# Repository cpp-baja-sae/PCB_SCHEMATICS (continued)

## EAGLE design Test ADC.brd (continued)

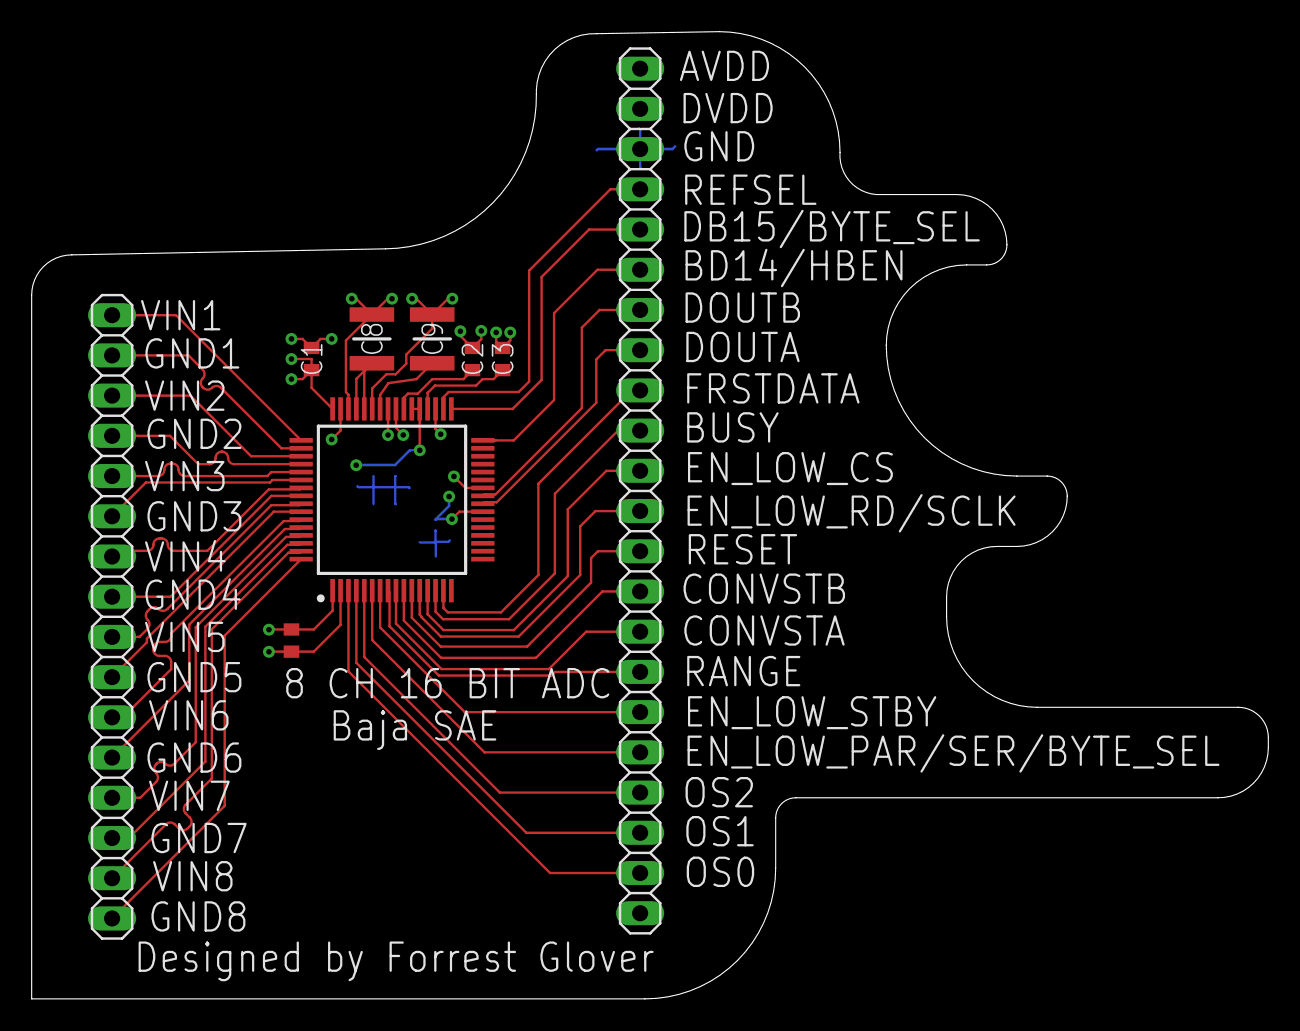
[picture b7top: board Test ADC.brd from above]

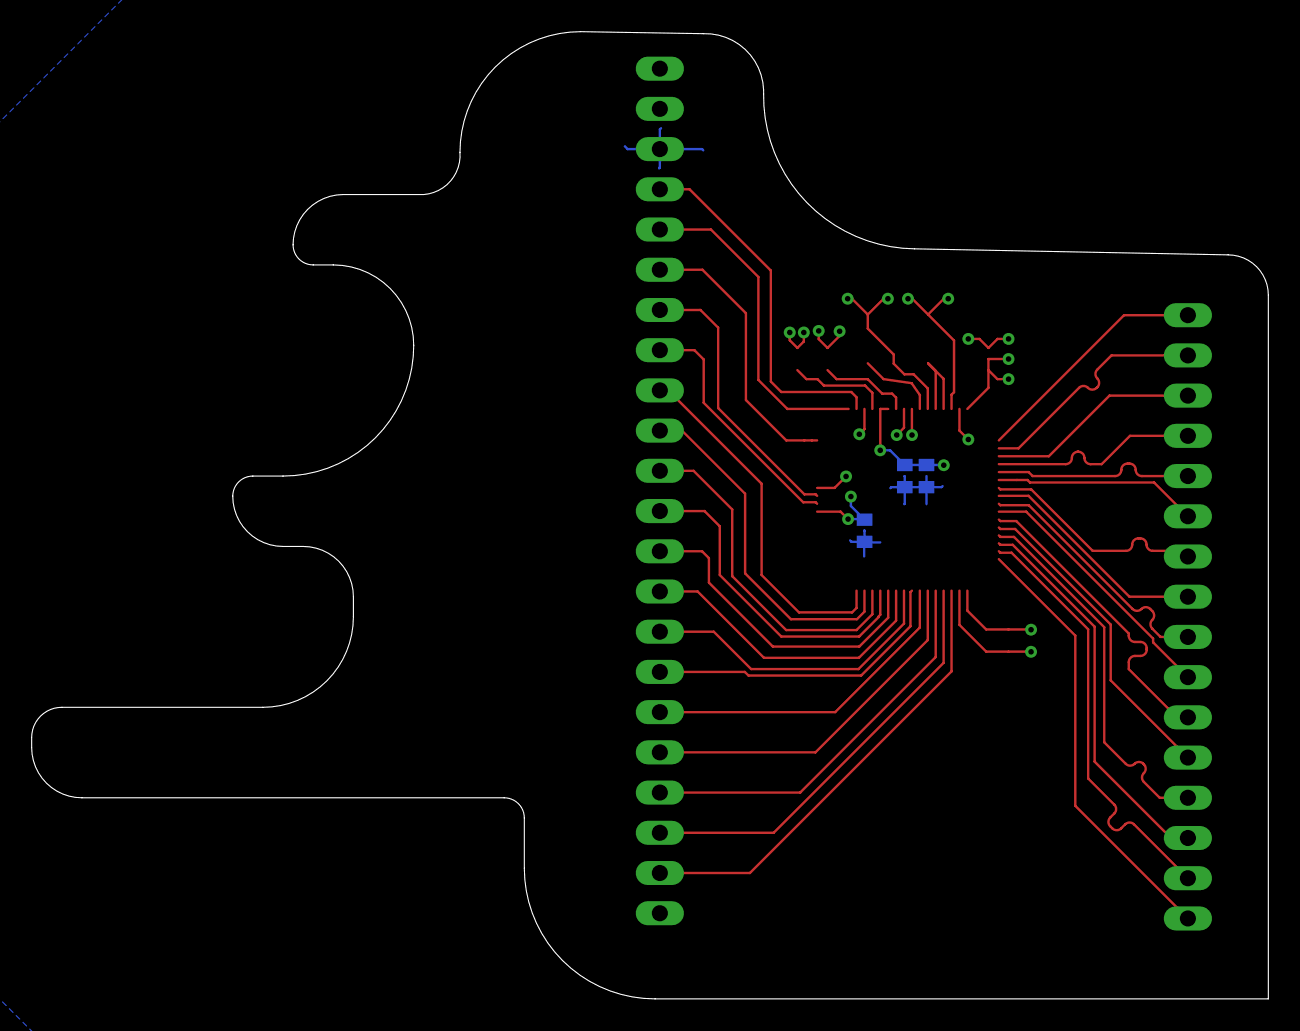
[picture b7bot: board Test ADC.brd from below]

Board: 4 copper layers, 78.1 x 61.1 mm, 12 parts (3 on the bottom side), 41 nets.

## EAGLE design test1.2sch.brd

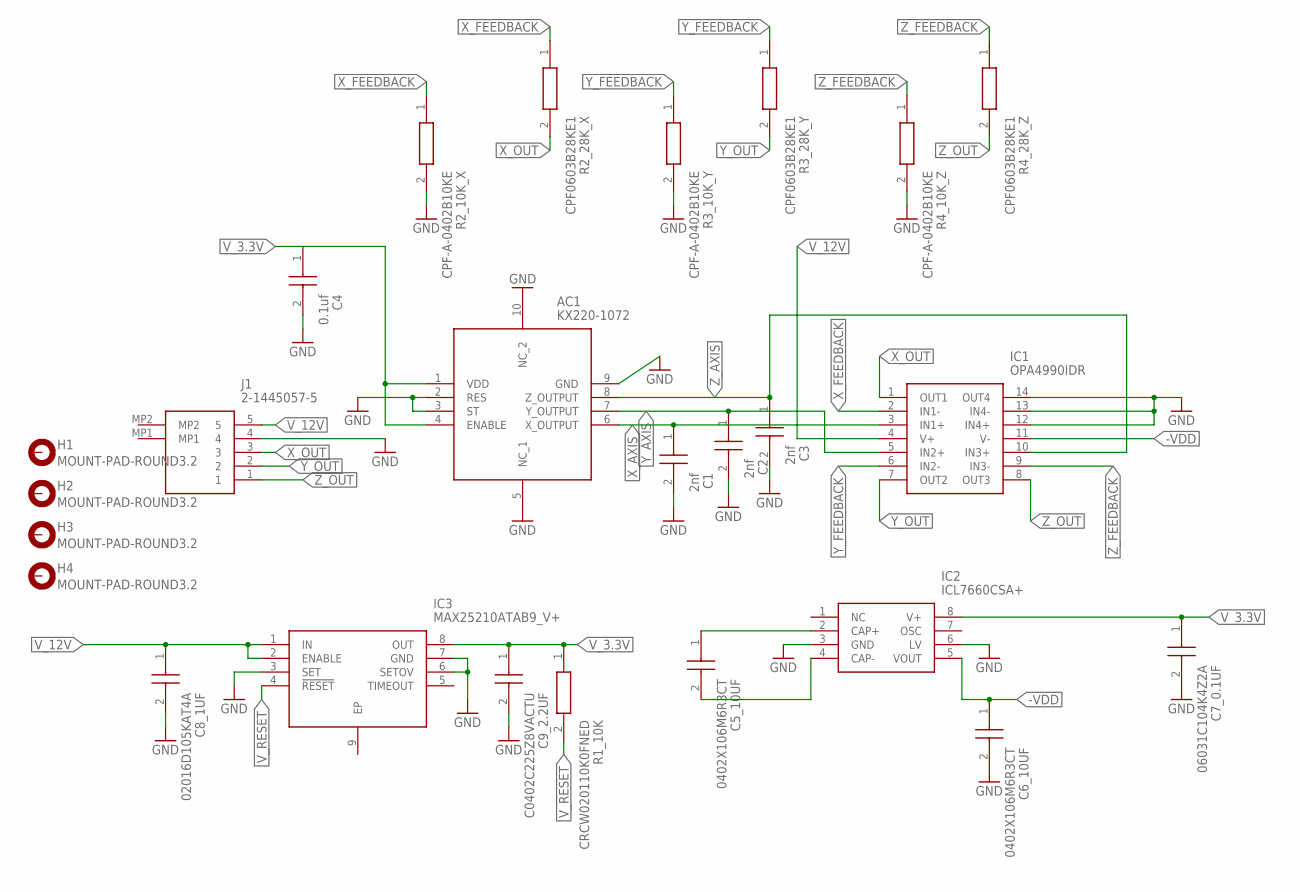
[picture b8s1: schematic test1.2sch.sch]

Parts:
AC1: KX220-1072; KX2201072
C1, C2, C3: 2nf; CAPC1005X60N
C4: 0.1uf; CAPC1608X90N
C5_10UF, C6_10UF: 0402X106M6R3CT; CAPC1005X55N
C7_0.1UF: 06031C104K4Z2A; CAPC1608X90N
C8_1UF: 02016D105KAT4A; CAPC0603X33N
C9_2.2UF: C0402C225Z8VACTU; INDC1005X55N
H1, H2, H3, H4: MOUNT-PAD-ROUND3.2; 3,2-PAD
IC1: OPA4990IDR; SOIC127P600X175-14N
IC2: ICL7660CSA+; SOIC127P600X175-8N
IC3: MAX25210ATAB9_V+; SON65P300X300X80-9N
J1: 2-1445057-5; 214450575
R1_10K: CRCW020110K0FNED; RESC0603X28N
R2_10K_X, R3_10K_Y, R4_10K_Z: CPF-A-0402B10KE; RESC1005X35N
R2_28K_X, R3_28K_Y, R4_28K_Z: CPF0603B28KE1; RESC1608X55N

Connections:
-VDD: C6_10UF.1, IC1.11 (V-), IC2.5 (VOUT)
GND: AC1.2 (RES), AC1.3 (ST), AC1.5 (NC_1), AC1.9 (GND), AC1.10 (NC_2), C1.2 (C2), C2.2 (C2), C3.2 (C2), C4.2, C6_10UF.2, C7_0.1UF.2, C8_1UF.2, C9_2.2UF.2, IC1.12 (IN4+), IC1.13 (IN4-), IC1.14 (OUT4), IC2.3 (GND), IC2.6 (LV), IC3.3 (SET), IC3.6 (SETOV), IC3.7 (GND), J1.4, R2_10K_X.2, R3_10K_Y.2, R4_10K_Z.2
unnamed: C5_10UF.1, IC2.2 (CAP+)
unnamed: C5_10UF.2, IC2.4 (CAP-)
V_3.3V: AC1.1 (VDD), AC1.4 (ENABLE), C4.1, C7_0.1UF.1, C9_2.2UF.1, IC2.8 (V+), IC3.8 (OUT), R1_10K.1
V_12V: C8_1UF.1, IC1.4 (V+), IC3.1 (IN), IC3.2 (ENABLE), J1.5
V_RESET: IC3.4 (!RESET), R1_10K.2
X_AXIS: AC1.6 (X_OUTPUT), C1.1 (C1), IC1.3 (IN1+)
X_FEEDBACK: IC1.2 (IN1-), R2_10K_X.1, R2_28K_X.1
X_OUT: IC1.1 (OUT1), J1.3, R2_28K_X.2
Y_AXIS: AC1.7 (Y_OUTPUT), C2.1 (C1), IC1.5 (IN2+)
Y_FEEDBACK: IC1.6 (IN2-), R3_10K_Y.1, R3_28K_Y.1
Y_OUT: IC1.7 (OUT2), J1.2, R3_28K_Y.2
Z_AXIS: AC1.8 (Z_OUTPUT), C3.1 (C1), IC1.10 (IN3+)
Z_FEEDBACK: IC1.9 (IN3-), R4_10K_Z.1, R4_28K_Z.1
Z_OUT: IC1.8 (OUT3), J1.1, R4_28K_Z.2

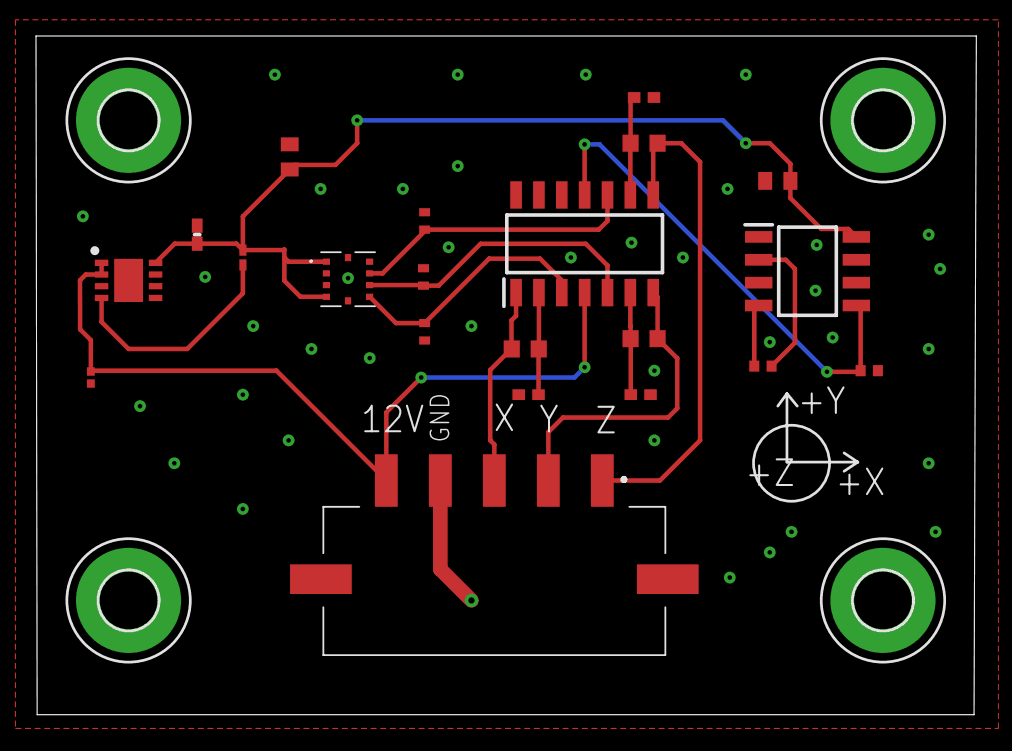
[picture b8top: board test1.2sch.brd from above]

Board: 2 copper layers, 52.2 x 37.7 mm, 25 parts (0 on the bottom side), 16 nets.
